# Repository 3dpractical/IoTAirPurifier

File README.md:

# IoTAirPurifier
Air Purifier Based on IoT with UV, Ozone, and Hepa Filter for filtering. Compatible controlled by Web Based, Manual Interface (Button), and IR Remote Control. This project is named Airings.

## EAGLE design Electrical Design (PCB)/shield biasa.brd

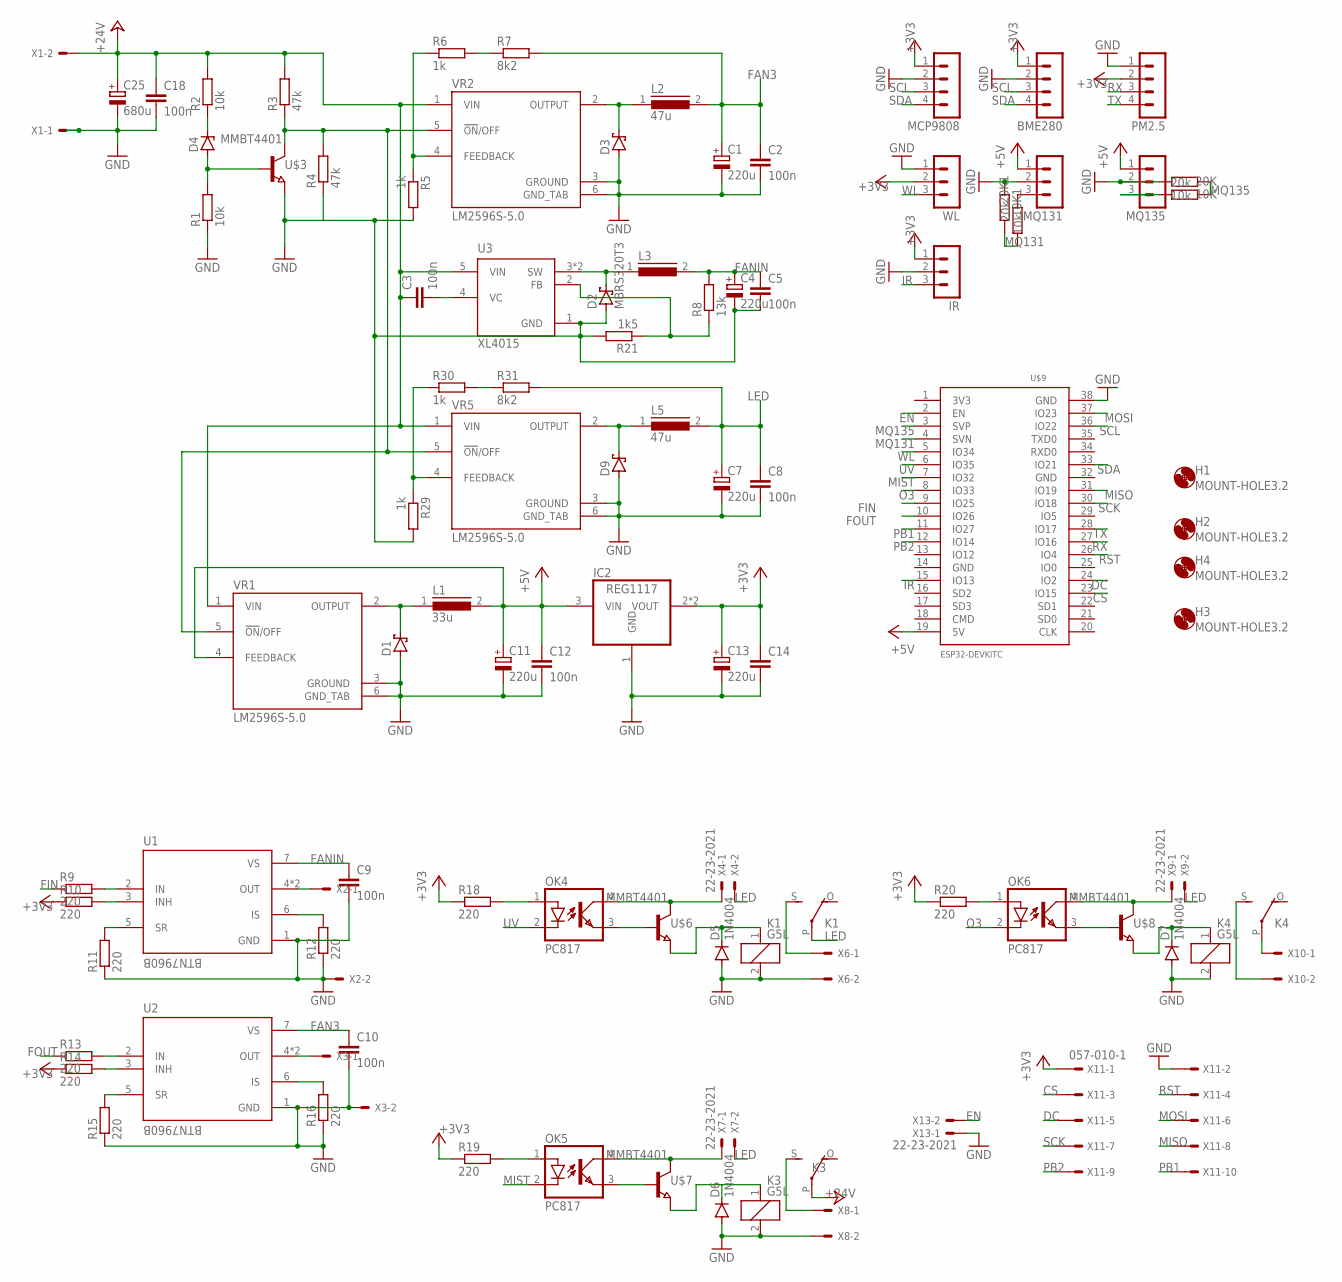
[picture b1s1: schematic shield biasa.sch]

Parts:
10K, 10K1: 10k; R0805
20K, 20K1: 20k; R0805
BME280: MA04-1
C1, C4, C7, C11, C13: 220u; 153CLV-0605
C2, C3, C5, C8, C9, C10, C12, C14, C18: 100n; C0805
C25: 680u; 150CLZ-1010
D1, D3, D9: SCHOTTKY-DIODESMD; SMB
D2: MBRS320T3; SMC
D4: ZENER-DIODESOD80C; SOD80C
D5, D6, D7: 1N4004; DO41-10
H1, H2, H3, H4: MOUNT-HOLE3.2; 3,2
IC2: REG1117; SOT223
IR: MA03-1
K1, K3, K4: G5L; G5LE
L1: 33u; DR125
L2, L5: 47u; DR125
L3: R1003DS11; S11-10
MCP9808: MA04-1
MQ131, MQ135: MA03-1
OK4, OK5, OK6: PC817; DIL04
PM2.5: MA04-1
R1, R2: 10k; R0805
R3, R4: 47k; R0805
R5, R6, R29, R30: 1k; R0805
R7, R31: 8k2; R0805
R8: 13k; R0805
R9, R10, R11, R12, R13, R14, R15, R16, R18, R19, R20: 220; R0805
R21: 1k5; R0805
U1, U2: BTN7960B; IC_BTN7960B
U3: XL4015; CONV_XL4015
U$3, U$6, U$7, U$8: MMBT4401; SOT23-RAEDEN
U$9: ESP32DEVKITC; ESP32-DEVKITC
VR1, VR2, VR5: LM2596S-5.0; TO170P1524X483-6N
WL: MA03-1
X1, X2, X3, X6, X8, X10: KK-156-2
X4, X7, X9, X13: 22-23-2021
X11: 057-010-1

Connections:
+3V3: BME280.1, C13.+, C14.1, IC2.2 (VOUT), IC2.4 (VOUT), IR.1, MCP9808.1, PM2.5.2, R10.1, R14.1, R18.1, R19.1, R20.1, WL.2, X11.1
+5V: C11.+, C12.1, IC2.3 (VIN), L1.2, MQ131.1, MQ135.1, U$9.19 (5V), VR1.4 (FEEDBACK)
+24V: C3.1, C18.1, C25.+, K3.P, R2.2, R3.2, U3.5 (VIN), VR1.1 (VIN), VR2.1 (VIN), VR5.1 (VIN), X1.2
CS: U$9.23 (IO15), X11.3
DC: U$9.24 (IO2), X11.5
EN: U$9.2 (EN), X13.2
FAN3: C1.+, C2.1, C10.1, L2.2, R7.2, U2.7 (VS)
FANIN: C4.+, C5.1, C9.1, L3.2, R8.2, U1.7 (VS)
FIN: R9.1, U$9.9 (IO25)
FOUT: R13.1, U$9.10 (IO26)
GND: 20K.2, 20K1.1, BME280.2, C1.-, C2.2, C4.-, C5.2, C7.-, C8.2, C9.2, C10.2, C11.-, C12.2, C13.-, C14.2, C18.2, C25.-, D1.A, D2.A, D3.A, D5.A, D6.A, D7.A, D9.A, IC2.1 (GND), IR.2, K1.2, K3.2, K4.2, MCP9808.2, MQ131.2, MQ135.2, PM2.5.1, R1.1, R4.1, R5.2, R11.1, R12.1, R15.1, R16.1, R21.2, R29.2, U1.1 (GND), U2.1 (GND), U3.1 (GND), U$3.E, U$9.38 (GND), VR1.3 (GROUND), VR1.6 (GND_TAB), VR2.3 (GROUND), VR2.6 (GND_TAB), VR5.3 (GROUND), VR5.6 (GND_TAB), WL.1, X1.1, X2.2, X3.2, X6.2, X8.2, X11.2, X13.1
IR: IR.3, U$9.15 (IO13)
LED: C7.+, C8.1, K1.P, L5.2, R31.2, X4.2, X7.2, X9.2
MISO: U$9.31 (IO19), X11.8
MIST: OK5.2 (C), U$9.7 (IO32)
MOSI: U$9.37 (IO23), X11.6
MQ131: 10K1.2, 20K1.2, U$9.4 (SVN)
MQ135: 10K.1, 20K.1, U$9.3 (SVP)
unnamed: D3.C, L2.1, VR2.2 (OUTPUT)
unnamed: D4.A, R1.2, U$3.B
unnamed: D4.C, R2.1
unnamed: R9.2, U1.2 (IN)
unnamed: R10.2, U1.3 (INH)
unnamed: R11.2, U1.5 (SR)
unnamed: D1.C, L1.1, VR1.2 (OUTPUT)
unnamed: 10K1.1, MQ131.3
unnamed: C3.2, U3.4 (VC)
unnamed: OK4.1 (A), R18.2
unnamed: R5.1, R6.1, VR2.4 (FEEDBACK)
unnamed: R12.2, U1.6 (IS)
unnamed: OK4.4 (COL), U$6.C, X4.1
unnamed: D2.C, L3.1, U3.3 (SW), U3.3.1 (SW)
unnamed: OK4.3 (EMIT), U$6.B
unnamed: D5.C, K1.1, U$6.E
unnamed: U1.4 (OUT), U1.8 (OUT), X2.1
unnamed: K4.S, X10.2
unnamed: R13.2, U2.2 (IN)
unnamed: R14.2, U2.3 (INH)
unnamed: K1.S, X6.1
unnamed: R15.2, U2.5 (SR)
unnamed: 10K.2, MQ135.3
unnamed: K4.P, X10.1
unnamed: R16.2, U2.6 (IS)
unnamed: K3.S, X8.1
unnamed: R8.1, R21.1, U3.2 (FB)
unnamed: U2.4 (OUT), U2.8 (OUT), X3.1
unnamed: OK5.1 (A), R19.2
unnamed: OK6.3 (EMIT), U$8.B
unnamed: OK6.4 (COL), U$8.C, X9.1
unnamed: D6.C, K3.1, U$7.E
unnamed: OK6.1 (A), R20.2
unnamed: OK5.3 (EMIT), U$7.B
unnamed: D7.C, K4.1, U$8.E
unnamed: OK5.4 (COL), U$7.C, X7.1
unnamed: R6.2, R7.1
unnamed: D9.C, L5.1, VR5.2 (OUTPUT)
unnamed: R3.1, R4.2, U$3.C, VR1.5 (!ON!/OFF), VR2.5 (!ON!/OFF), VR5.5 (!ON!/OFF)
unnamed: R29.1, R30.1, VR5.4 (FEEDBACK)
unnamed: R30.2, R31.1
O3: OK6.2 (C), U$9.8 (IO33)
PB1: U$9.11 (IO27), X11.10
PB2: U$9.12 (IO14), X11.9
RST: U$9.26 (IO4), X11.4
RX: PM2.5.3, U$9.27 (IO16)
SCK: U$9.30 (IO18), X11.7
SCL: BME280.3, MCP9808.3, U$9.36 (IO22)
SDA: BME280.4, MCP9808.4, U$9.33 (IO21)
TX: PM2.5.4, U$9.28 (IO17)
UV: OK4.2 (C), U$9.6 (IO35)
WL: U$9.5 (IO34), WL.3

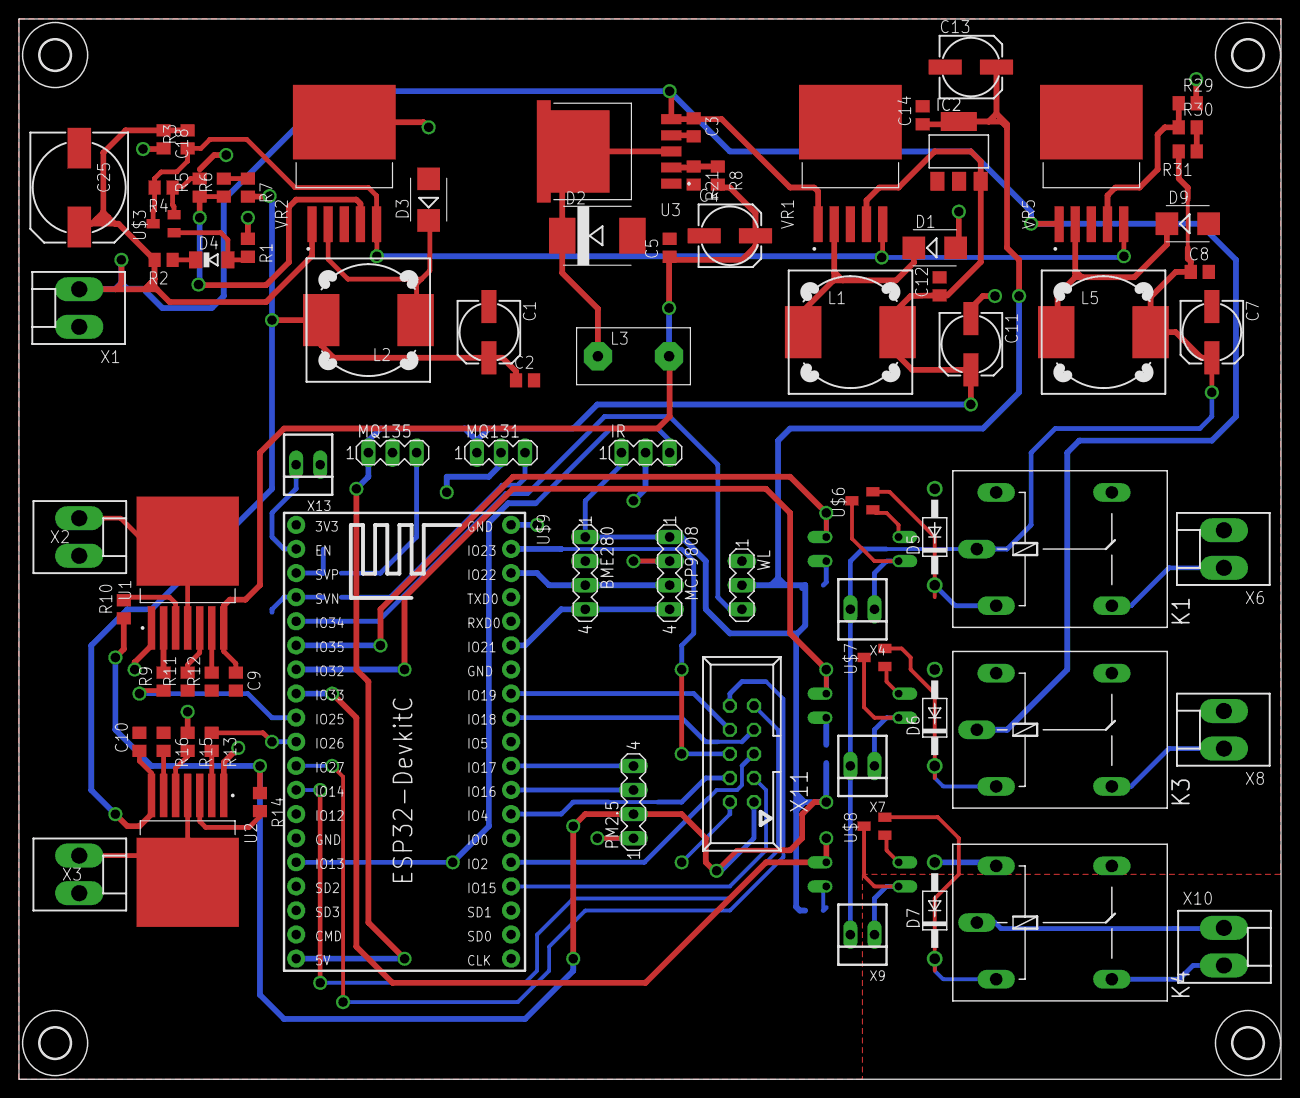
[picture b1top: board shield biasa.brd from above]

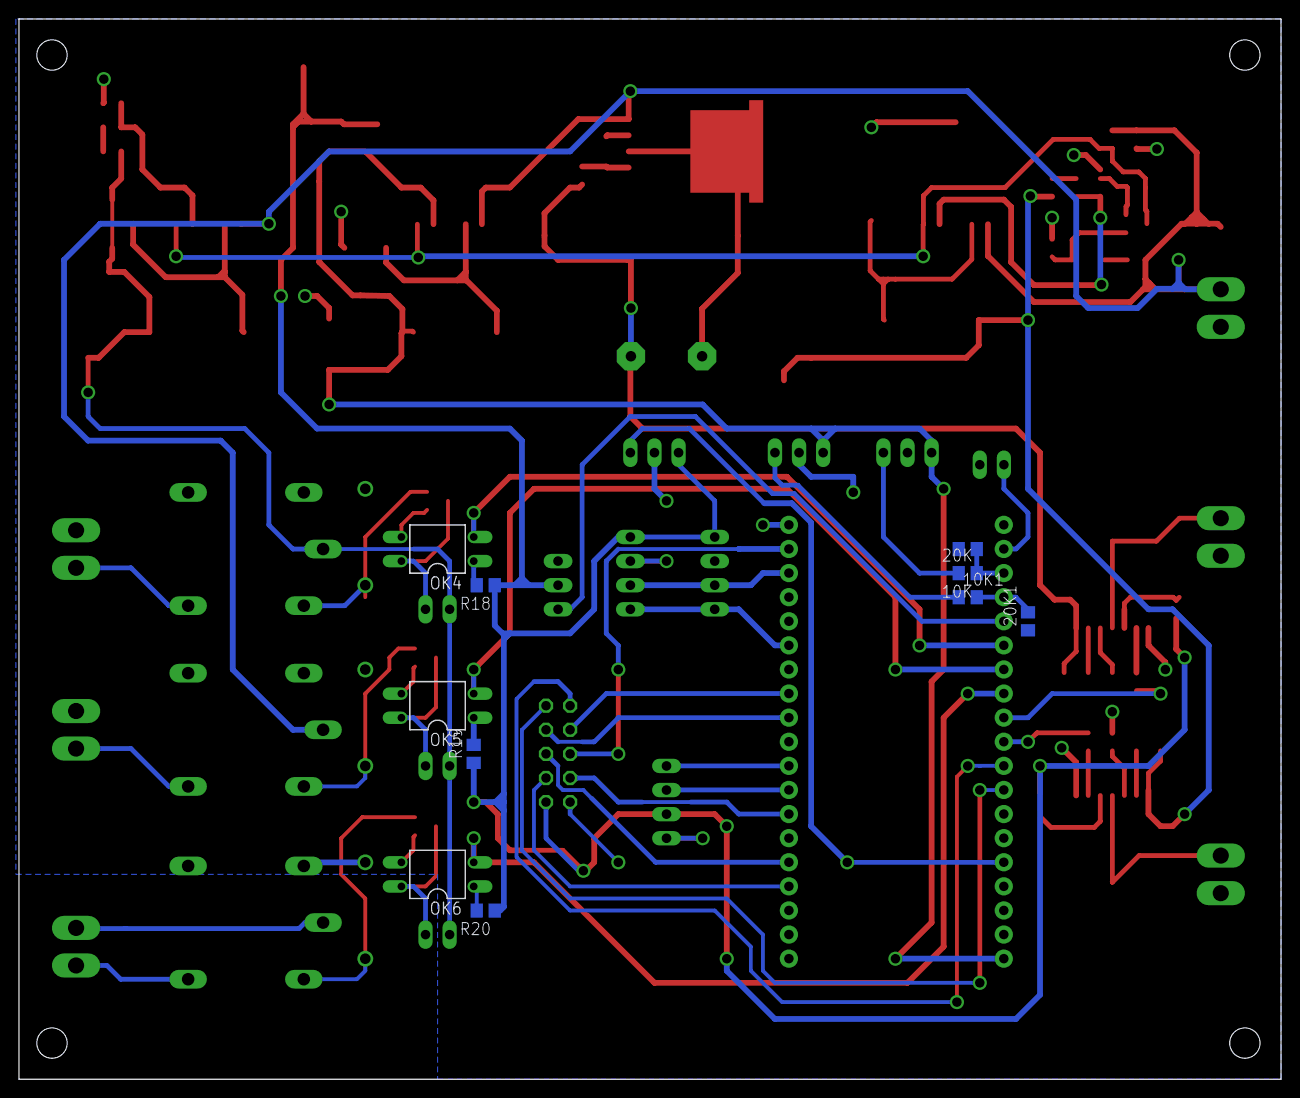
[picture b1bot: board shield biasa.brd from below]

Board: 2 copper layers, 133.0 x 111.8 mm, 94 parts (10 on the bottom side), 70 nets.
